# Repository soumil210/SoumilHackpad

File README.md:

# SoumilHackpad

project repository.

## Project Overview

- Hackpad name: SoumilHackpad
- Creator: soumil
- Description: My macropad has 9 keys, a small OLED, and a rotary encoder. I can use it for macros, volume control, or just for fun. :)

## Repository Structure

- `CAD/` - Full assembled hackpad model :)
- `PCB/` - PCB source design files 
- `Firmware/` - Firmware source files 
- `production/` - Manufacturing-ready outputs 

## Screenshots 

### 1. Overall Hackpad

### 2. Schematic

### 3. PCB

## BOM

| Item | Qty | Notes |
| --- | --- | --- |
| Seeed XIAO RP2040 (Through-hole, unsoldered) | 1 | Main MCU |
| 1N4148 Diodes (through-hole) | 9 | Through-hole diodes |
| MX-Style switches | 9 | Main key switches |
| EC11 Rotary encoders | 1 | Rotary input |
| 0.91 inch OLED display | 1 | Pin order must be `GND-VCC-SCL-SDA` |
| White blank DSA keycaps | 9 | For 16-key layout |
| SK6812 MINI-E LEDs | 9 | Per-key lighting |

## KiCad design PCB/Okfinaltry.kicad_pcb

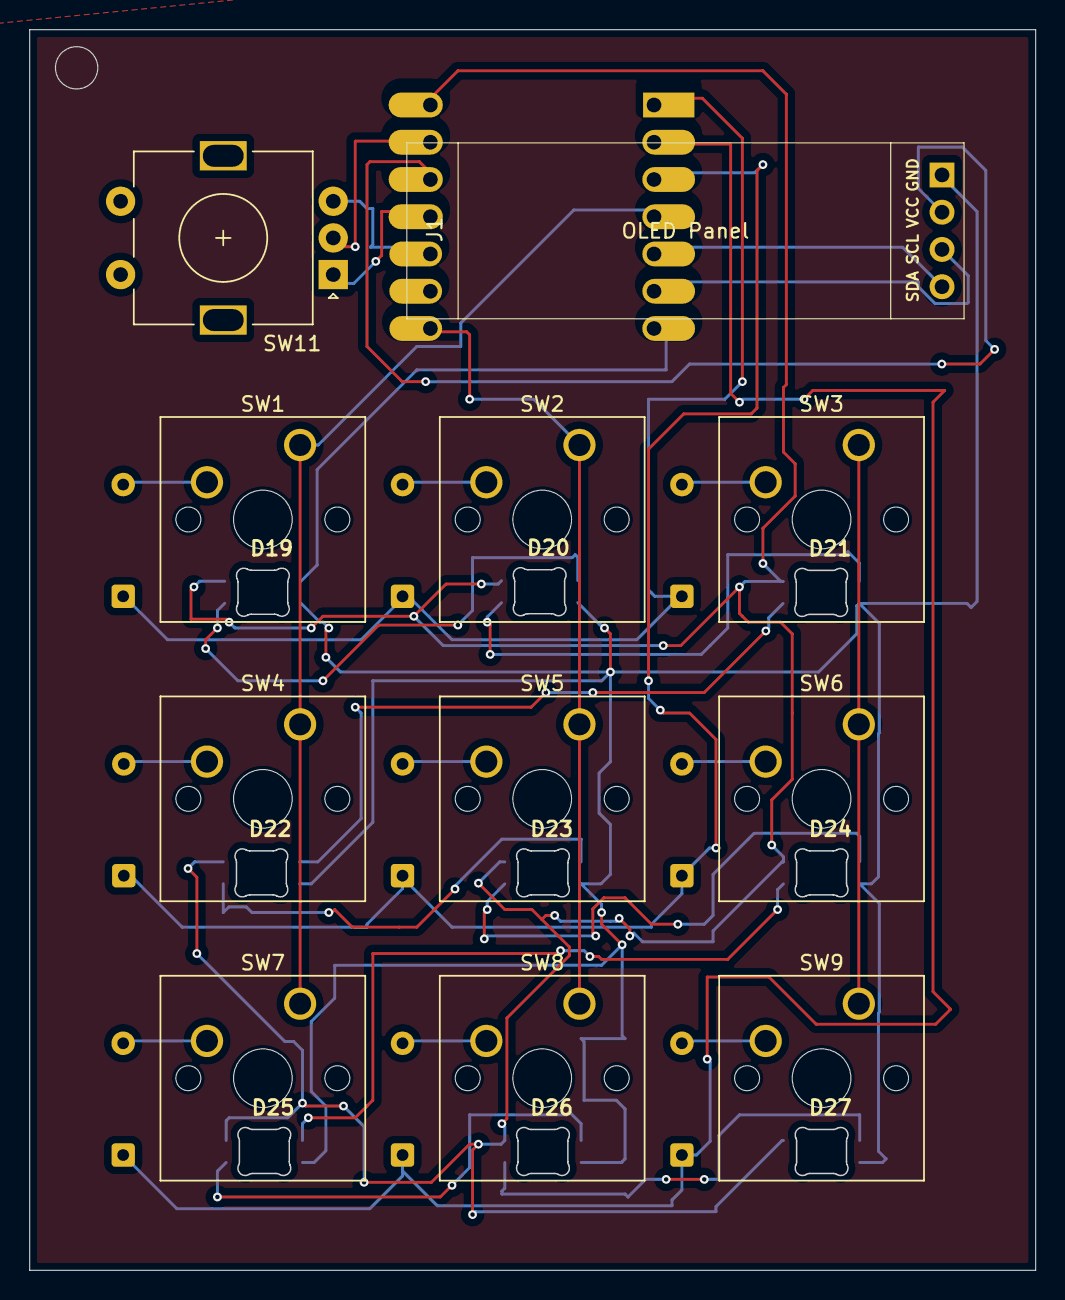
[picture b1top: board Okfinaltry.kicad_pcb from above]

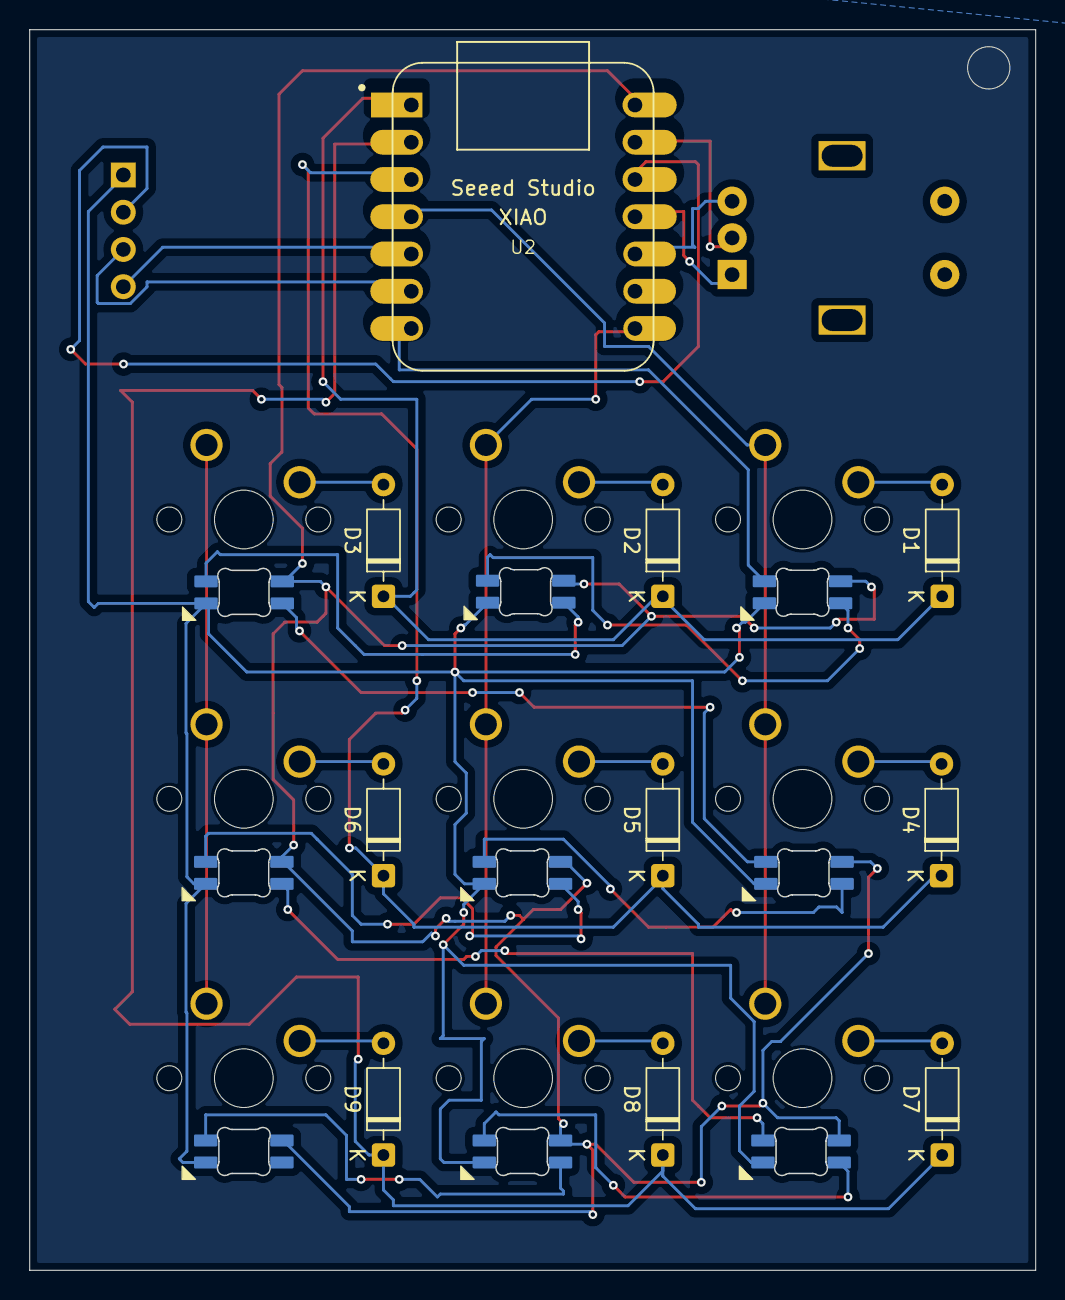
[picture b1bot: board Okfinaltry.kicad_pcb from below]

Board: 2 copper layers, 68.5 x 84.6 mm, 30 parts (10 on the bottom side), 31 nets.

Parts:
D1, D2, D3, D4, D5, D6, D7, D8, D9: 1N4148; D_DO-35_SOD27_P7.62mm_Horizontal
D19, D20, D21, D22, D23, D24, D25, D26, D27: SK6812MINI-E; SK6812MINI-E_fixed
J1: OLED_128x32; SSD1306-0.91-OLED-4pin-128x32
SW1, SW2, SW3, SW4, SW5, SW6, SW7, SW8, SW9: SW_Push_45deg; SW_Cherry_MX_1.00u_PCB
SW11: RotaryEncoder; RotaryEncoder_Alps_EC11E-Switch_Vertical_H20mm
U2: MOUDLE-SEEEDUINO-XIAO; XIAO-Generic-Hybrid-14P-2.54-21X17.8MM

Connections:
+3V3: J1.2 (VCC), U2.12 (3V3)
A: SW11.A, U2.11 (PA6_A10_D10_MOSI)
B: SW11.B, U2.10 (PA5_A9_D9_MISO)
Col 0: SW1.1, SW4.1, SW7.1, U2.4 (PA11_A3_D3)
GND: D19.3 (VSS), D20.3 (VSS), D21.3 (VSS), D22.3 (VSS), D23.3 (VSS), D24.3 (VSS), D25.3 (VSS), D26.3 (VSS), D27.3 (VSS), J1.1 (GND), SW11.C, U2.13 (GND)
unnamed: D1.2 (A), SW1.2
unnamed: D2.2 (A), SW2.2
unnamed: D3.2 (A), SW3.2
unnamed: D4.2 (A), SW4.2
unnamed: D5.2 (A), SW5.2
unnamed: D6.2 (A), SW6.2
unnamed: D7.2 (A), SW7.2
unnamed: D8.2 (A), SW8.2
unnamed: D9.2 (A), SW9.2
unnamed: D19.2 (DOUT), D20.4 (DIN)
unnamed: D20.2 (DOUT), D21.4 (DIN)
unnamed: D21.2 (DOUT), D22.4 (DIN)
unnamed: D22.2 (DOUT), D23.4 (DIN)
unnamed: D23.2 (DOUT), D24.4 (DIN)
unnamed: D24.2 (DOUT), D25.4 (DIN)
unnamed: D25.2 (DOUT), D26.4 (DIN)
unnamed: D26.2 (DOUT), D27.4 (DIN)
Row 0: D1.1 (K), D2.1 (K), D3.1 (K), U2.1 (PA02_A0_D0)
Row 1: D4.1 (K), D5.1 (K), D6.1 (K), U2.3 (PA10_A2_D2)
Row 2: D7.1 (K), D8.1 (K), D9.1 (K), U2.2 (PA4_A1_D1)
SCL: J1.3 (SCL), U2.6 (PA9_A5_D5_SCL)
SDA: J1.4 (SDA), U2.5 (PA8_A4_D4_SDA)
Sk6812Mini-e: D19.4 (DIN), U2.7 (PB08_A6_D6_TX)
VCC: D19.1 (VDD), D20.1 (VDD), D21.1 (VDD), D22.1 (VDD), D23.1 (VDD), D24.1 (VDD), D25.1 (VDD), D26.1 (VDD), D27.1 (VDD), U2.14 (5V)
col 1: SW2.1, SW5.1, SW8.1, U2.8 (PB09_A7_D7_RX)
col 2: SW3.1, SW6.1, SW9.1, U2.9 (PA7_A8_D8_SCK)

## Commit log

2026-03-31 Set up Blueprint hackpad repository structure
2026-03-31 Add current CAD, PCB, and production assets
2026-03-31 Link README screenshots to repository images
2026-03-31 Add README screenshot image assets
2026-03-31 Update BOM with finalized component list
2026-03-31 Remove part number column from BOM
2026-03-31 Remove unnecessary .gitkeep placeholders
2026-03-31 Add current remaining local files
2026-03-31 Add firmware Main.py
2026-03-31 Remove Firmware .gitkeep placeholder
2026-03-31 Add production main.py copy
2026-03-31 Add production copy of CAD STEP file
2026-03-31 Revise project details and clean up README.md
    Updated project description and creator name in README.md. Removed unnecessary sections and added required screenshots.
2026-04-03 Fix formatting in README for case parts requirement
2026-04-08 Update README to remove design constraints
    Removed required design constraints section from README.
2026-05-20 Fix typo in README.md
2026-06-20 Add initial keyboard firmware setup
2026-06-20 Add Diagnosev1 for manual matrix key scanning
2026-06-20 Add firmware for manual matrix key scanning
2026-06-24 Add rotary encoder test script
2026-06-24 Create Testrotaryencoder
